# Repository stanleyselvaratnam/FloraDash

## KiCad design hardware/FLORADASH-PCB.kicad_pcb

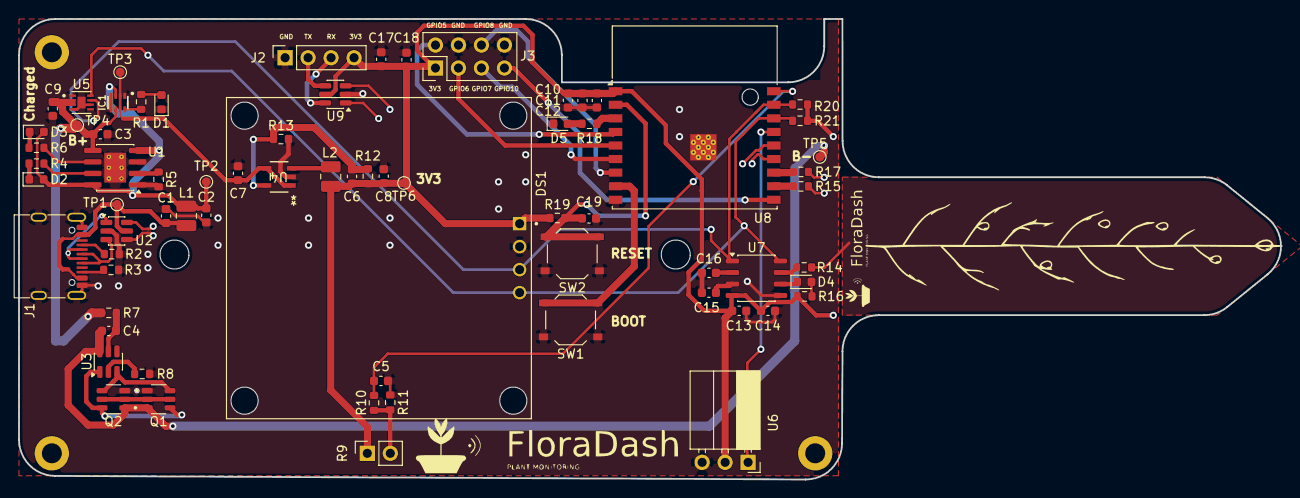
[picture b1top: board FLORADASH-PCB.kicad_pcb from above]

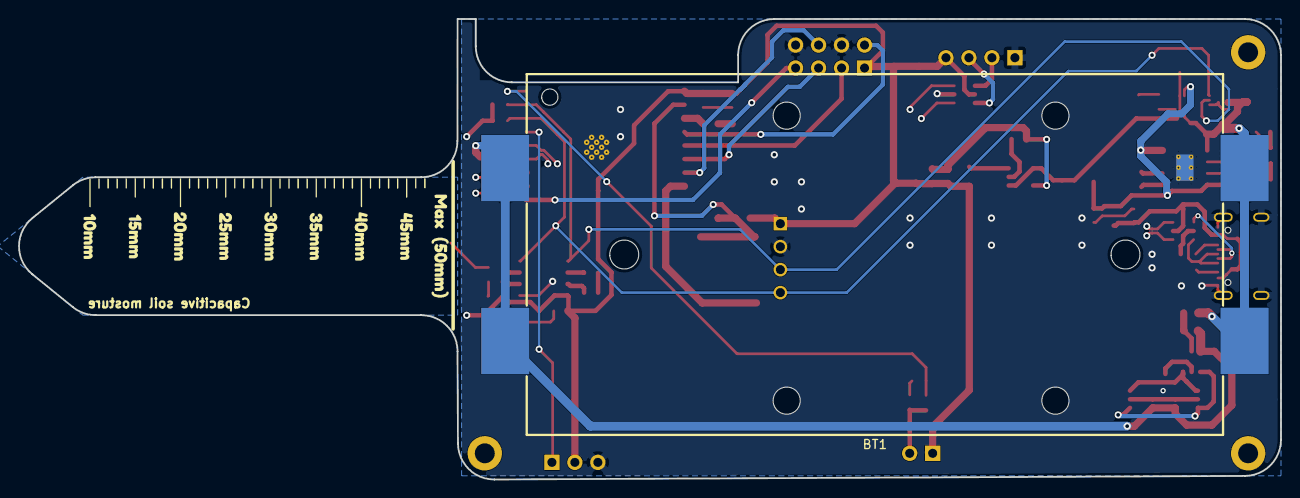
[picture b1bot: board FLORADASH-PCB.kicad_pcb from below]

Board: 4 copper layers, 139.5 x 50.9 mm, 84 parts (10 on the bottom side), 52 nets.

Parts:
BT1: BAT-SMD_BH-18650-B1BA007
C1, C2, C4, C5, C9, C13, C15, C17, C18, C19: 100n; C_0603_1608Metric
C3: 10u; C_0603_1608Metric
C6: 22p; C_0603_1608Metric
C7, C8, C10, C11, C12: 22u; C_0603_1608Metric
C14: 1u; C_0603_1608Metric
C16: 2n2; C_0603_1608Metric
D1, D4: LED BLUE; D_0603_1608Metric
D2: LED RED; D_0603_1608Metric
D3: LED GREEN; D_0603_1608Metric
D5: LED YELLOW; D_0603_1608Metric
DS1: OLED_128X64_1.3_I2C; LCD_OLED_128X64_1.3_I2C
H1, H2, H3: MountingHole; MountingHole_2.2mm_M2_DIN965_Pad
IC1: LM66200DRLR; SOT8
J1: USB_C_Receptacle_USB2.0_16P; USB_C_Receptacle_G-Switch_GT-USB-7010ASV
J2: Conn_01x04_Pin; PinSocket_1x04_P2.54mm_Vertical
J3: Conn_02x04_Top_Bottom; PinHeader_2x04_P2.54mm_Vertical
L1, L2: 2u2; L_1008_2520Metric
Q1, Q2: FS8205; SOT95P280X145-6N
R1, R4, R6, R8, R10, R18: 1k; R_0603_1608Metric
R2, R3, R19: 5.1k; R_0603_1608Metric
R5: 1.2k; R_0603_1608Metric
R7: 100; R_0603_1608Metric
R9: GL5528; PinSocket_1x02_P2.54mm_Vertical
R11: 10k; R_0603_1608Metric
R12: 267k; R_0603_1608Metric
R13: 59k; R_0603_1608Metric
R14: 560; R_0603_1608Metric
R15, R17: 47; R_0603_1608Metric
R16: 2.2k; R_0603_1608Metric
R20, R21: 4.7k; R_0603_1608Metric
SW1, SW2: SW_Push; SW_Push_1P1T_XKB_TS-1187A
TP1, TP2, TP3, TP4, TP5, TP6: TestPoint; TestPoint_Pad_D1.0mm
U1: TP4056-42-ESOP8; SOIC-8-1EP_3.9x4.9mm_P1.27mm_EP2.41x3.3mm_ThermalVias
U2, U9: USBLC6-2SC6; SOT-23-6
U3: DW01A; SOT-23-6
U4: SY8089AAAC_SGY
U5: MAX17048G_T10; SON50P200X200X80-9N
U6: DHT11; PinSocket_1x03_P2.54mm_Horizontal
U7: CY8CMBR3102; JEITA_SOIC-8_3.9x4.9mm_P1.27mm
U8: ESP32-C3-WROOM-02
kibuzzard-69837BBB: G***; kibuzzard-69837BBB
kibuzzard-69837BD1: G***; kibuzzard-69837BD1
kibuzzard-69837BDA: G***; kibuzzard-69837BDA
kibuzzard-69837BE0: G***; kibuzzard-69837BE0
kibuzzard-69837BE5: G***; kibuzzard-69837BE5
kibuzzard-69837BE9: G***; kibuzzard-69837BE9
kibuzzard-69837BEE: G***; kibuzzard-69837BEE
kibuzzard-69837BF5: G***; kibuzzard-69837BF5
kibuzzard-6983799B: G***; kibuzzard-6983799B

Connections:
+3.3V: C6.1, C8.1, C10.1, C11.1, C12.1, C13.1, C14.1, C17.1, C18.1, DS1.1 (VDD), J2.4, J3.1, L2.2, R9.1, R12.2, R16.2, R19.2, R20.1, R21.1, TP6.1 (1_1), U6.2 (VCC), U7.4 (VDD), U8.1 (3V3), U9.5 (VBUS)
+5V: C1.1, J1.A4 (VBUS), J1.A9 (VBUS), J1.B4 (VBUS), J1.B9 (VBUS), L1.1, TP1.1 (1_1), U2.5 (VBUS)
+5V_FILT: C2.1, D2.2 (A), D3.2 (A), IC1.3 (VIN1), L1.2, TP2.1 (1_1), U1.4 (V_{CC}), U1.8 (CE)
ADC_LUX: C5.1, R10.1, U8.18 (IO0)
BOOT: SW1.2, U8.8 (IO9)
Bat+: BT1.1, BT1.3, C3.1, C9.1, IC1.6 (VIN2), R7.1, TP4.1 (1_1), U1.5 (BAT), U5.2 (CELL), U5.3 (VDD)
Bat-: BT1.2, BT1.4, C4.2, Q1.3, Q2.1, TP5.1 (1_1), U3.6 (GND)
D+: U2.4 (I/O2), U8.14 (IO19)
D-: U2.6 (I/O1), U8.13 (IO18)
GND: C1.2, C2.2, C3.2, C5.2, C7.2, C8.2, C9.2, C10.2, C11.2, C12.2, C13.2, C14.2, C15.2, C16.2, C17.2, C18.2, C19.2, D1.1 (K), D5.1 (K), DS1.2 (GND), IC1.1 (GND@1), IC1.4 (ON), IC1.5 (GND@2), J1.A1 (GND), J1.A12 (GND), J1.B1 (GND), J1.B12 (GND), J1.SH (SHIELD), J2.1, J3.4, J3.8, Q1.1, Q2.3, R2.1, R3.2, R5.2, R8.2, R11.1, R13.1, SW1.1, SW2.1, U1.1 (TEMP), U1.3 (GND), U1.9 (EPAD), U2.2 (GND), U4.2 (GND), U5.1 (CTG), U5.4 (GND), U5.6 (QSTRT), U5.9 (EP), U6.3 (GND), U7.5 (GND), U8.9 (GND), U8.19 (GND), U9.2 (GND)
GPIO5: J3.2, U8.4 (IO5)
GPIO6: J3.3, U8.5 (IO6)
GPIO7: J3.5, U8.6 (IO7)
GPIO8: J3.6, U8.7 (IO8)
GPIO10: J3.7, U8.10 (IO10)
unnamed: D1.2 (A), R1.1
unnamed: D2.1 (K), R4.1
unnamed: D3.1 (K), R6.1
unnamed: D4.2 (A), R16.1
unnamed: D4.1 (K), U7.6 (GPO0/CS1)
unnamed: D5.2 (A), R18.1
unnamed: IC1.8 (ST), R1.2
unnamed: J1.A5 (CC1), R2.2
unnamed: J1.B5 (CC2), R3.1
unnamed: J1.A6 (D+), J1.B6 (D+), U2.3 (I/O2)
unnamed: J1.A7 (D-), J1.B7 (D-), U2.1 (I/O1)
unnamed: J2.2, U9.4 (I/O2)
unnamed: J2.3, U9.6 (I/O1)
unnamed: Q1.2, Q1.5, Q2.2, Q2.5
unnamed: R9.2, R10.2, R11.2
unnamed: R5.1, U1.2 (PROG)
unnamed: R4.2, U1.7 (~CHRG)
unnamed: R6.2, U1.6 (~STDBY)
unnamed: R8.1, U3.2 (CS)
unnamed: Q1.6, Q2.4, U3.3 (OC)
unnamed: Q1.4, Q2.6, U3.1 (OD)
unnamed: C4.1, R7.2, U3.5 (VCC)
unnamed: C6.2, R12.1, R13.2, U4.5 (FB)
unnamed: L2.1, U4.3 (LX)
unnamed: C16.1, U7.2 (CMOD)
unnamed: R14.1, U7.7 (CS0)
unnamed: C15.1, U7.3 (VCC)
unnamed: R18.2, U8.3 (IO4)
unnamed: R15.1, U8.11 (IO20/RXD)
unnamed: R17.1, U8.12 (IO21/TXD)
RST: C19.1, R19.1, SW2.2, U8.2 (EN)
RX: R15.2, U9.1 (I/O1)
SCL: DS1.3 (SCK), R20.2, U5.7 (SCL), U7.1 (SCL), U8.17 (IO1)
SDA: DS1.4 (SDA), R21.2, U5.8 (SDA), U7.8 (SDA), U8.16 (IO2)
TEMP/HUM: U6.1 (Data), U8.15 (IO3)
TX: R17.2, U9.3 (I/O2)
battery/usb: C7.1, IC1.2 (VOUT@1), IC1.7 (VOUT@2), TP3.1 (1_1), U4.1 (EN), U4.4 (IN)

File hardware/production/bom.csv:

Designator,Footprint,Quantity,Value,LCSC Part #
BT1,BAT-SMD_BH-18650-B1BA007,1,~,C6937126
"C1, C13, C15, C17, C18, C19, C2, C4, C5, C9",0603,10,100n,C14663
"C10, C11, C12, C7, C8",0603,5,22u,C59461
C14,0603,1,1u,C15849
C16,0603,1,2n2,C1604
C3,0603,1,10u,C19702
C6,0603,1,22p,C1653
"D1, D4",0603,2,LED BLUE,C2288
D2,0603,1,LED RED,C2286
D3,0603,1,LED GREEN,C12624
D5,0603,1,LED YELLOW,C111340
DS1,LCD_OLED_128X64_1.3_I2C,1,OLED_128X64_1.3_I2C,C2718488
IC1,SOT8,1,LM66200DRLR,C3235556
J1,USB_C_Receptacle_G-Switch_GT-USB-7010ASV,1,USB_C_Receptacle_USB2.0_16P,C2765186
J2,PinSocket_1x04_P2.54mm_Vertical,1,Conn_01x04_Pin,C2718488
J3,PinHeader_2x04_P2.54mm_Vertical,1,Conn_02x04_Top_Bottom,C225519 
"L1, L2",1008,2,2u2,C354538
"Q1, Q2",SOT95P280X145-6N,2,FS8205,C908265
"R1, R10, R18, R4, R6, R8",0603,6,1k,C21190
R11,0603,1,10k,C25804
R12,0603,1,267k,C2998118
R13,0603,1,59k,C177513
R14,0603,1,560,C23204
"R15, R17",0603,2,47,C23182
R16,0603,1,2.2k,C4190
"R19, R2, R3",0603,3,5.1k,C23186
"R20, R21",0603,2,4.7k,C23162
R5,0603,1,1.2k,C22765
R7,0603,1,100,C22775
R9,PinSocket_1x02_P2.54mm_Vertical,1,GL5528,C49661
"SW1, SW2",SW_Push_1P1T_XKB_TS-1187A,2,SW_Push,C778172
U1,SOIC-8-1EP_3.9x4.9mm_P1.27mm_EP2.41x3.3mm_ThermalVias,1,TP4056-42-ESOP8,C16581
"U2, U9",SOT-23-6,2,USBLC6-2SC6,C7519
U3,SOT-23-6,1,DW01A,C351410
U4,SY8089AAAC_SGY,1,~,
U5,SON50P200X200X80-9N,1,MAX17048G_T10,C2682616
U6,PinSocket_1x03_P2.54mm_Horizontal,1,DHT11,C22438144
U7,JEITA_SOIC-8_3.9x4.9mm_P1.27mm,1,CY8CMBR3102,C2759924
U8,ESP32-C3-WROOM-02,1,ESP32-C3-WROOM-02,C2934560

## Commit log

2026-04-17 Added the DHT11 Module
2026-04-18 New labels
2026-04-19 Cleaned the repo
2026-04-19 Example of schematic
2026-04-19 Added the Soil Moisture Sensor and LDR Sensor
2026-04-20 Added the Screen OLED footprint
2026-04-21 Added the Switch and low pass filter
2026-04-22 Added the pull-up I2C and logo
2026-04-25 Clean up schema
2026-04-25 Clean up the GPIOs add TVS protection
2026-04-26 New librairies for symbols
2026-04-26 New footprint - Battery and Screen
2026-04-26 Started the PCB and rules
2026-04-27 Routing structure
2026-05-01 Added the soil moisture sensor on PCB
2026-05-02 Placement of the Cap Sense
2026-05-08 Placement of components on PCB
2026-05-08 Added ground plane
2026-05-09 signal routing
2026-05-10 Routing PCB v2
2026-05-11 new calculated signals track width
2026-05-12 finish the first routing
2026-05-12 PCB customization
2026-05-12 Fixed all DRC constraint
2026-05-12 Added the sillkcreen def
2026-05-16 Finished the footprint assignation and PCB
2026-05-19 New symbol for regulator
2026-05-19 New footprint for regulator
2026-05-19 Generated Gerber files
2026-05-19 Finished routing PCB
2026-06-03 New component for buck converter
2026-06-03 Started the firmware of ESP32
2026-06-03 test: successful board flashing
2026-06-03 test: successful soil moisture driver
2026-06-05 test: successful with EZ-CLick configuration for the CapSense
2026-06-05 test: successful with humidity and temperature sensor - DHT11 library
2026-06-05 Clean the main code
2026-06-10 Used periodic interrupt for aquisition task
2026-06-11 display time optimization
2026-06-12 use RMT to prevent CPU blocking
2026-06-12 add the wake-up function to avoid the sleep mode of CapSense
2026-06-12 Integrated the sensor optimization in the main code
